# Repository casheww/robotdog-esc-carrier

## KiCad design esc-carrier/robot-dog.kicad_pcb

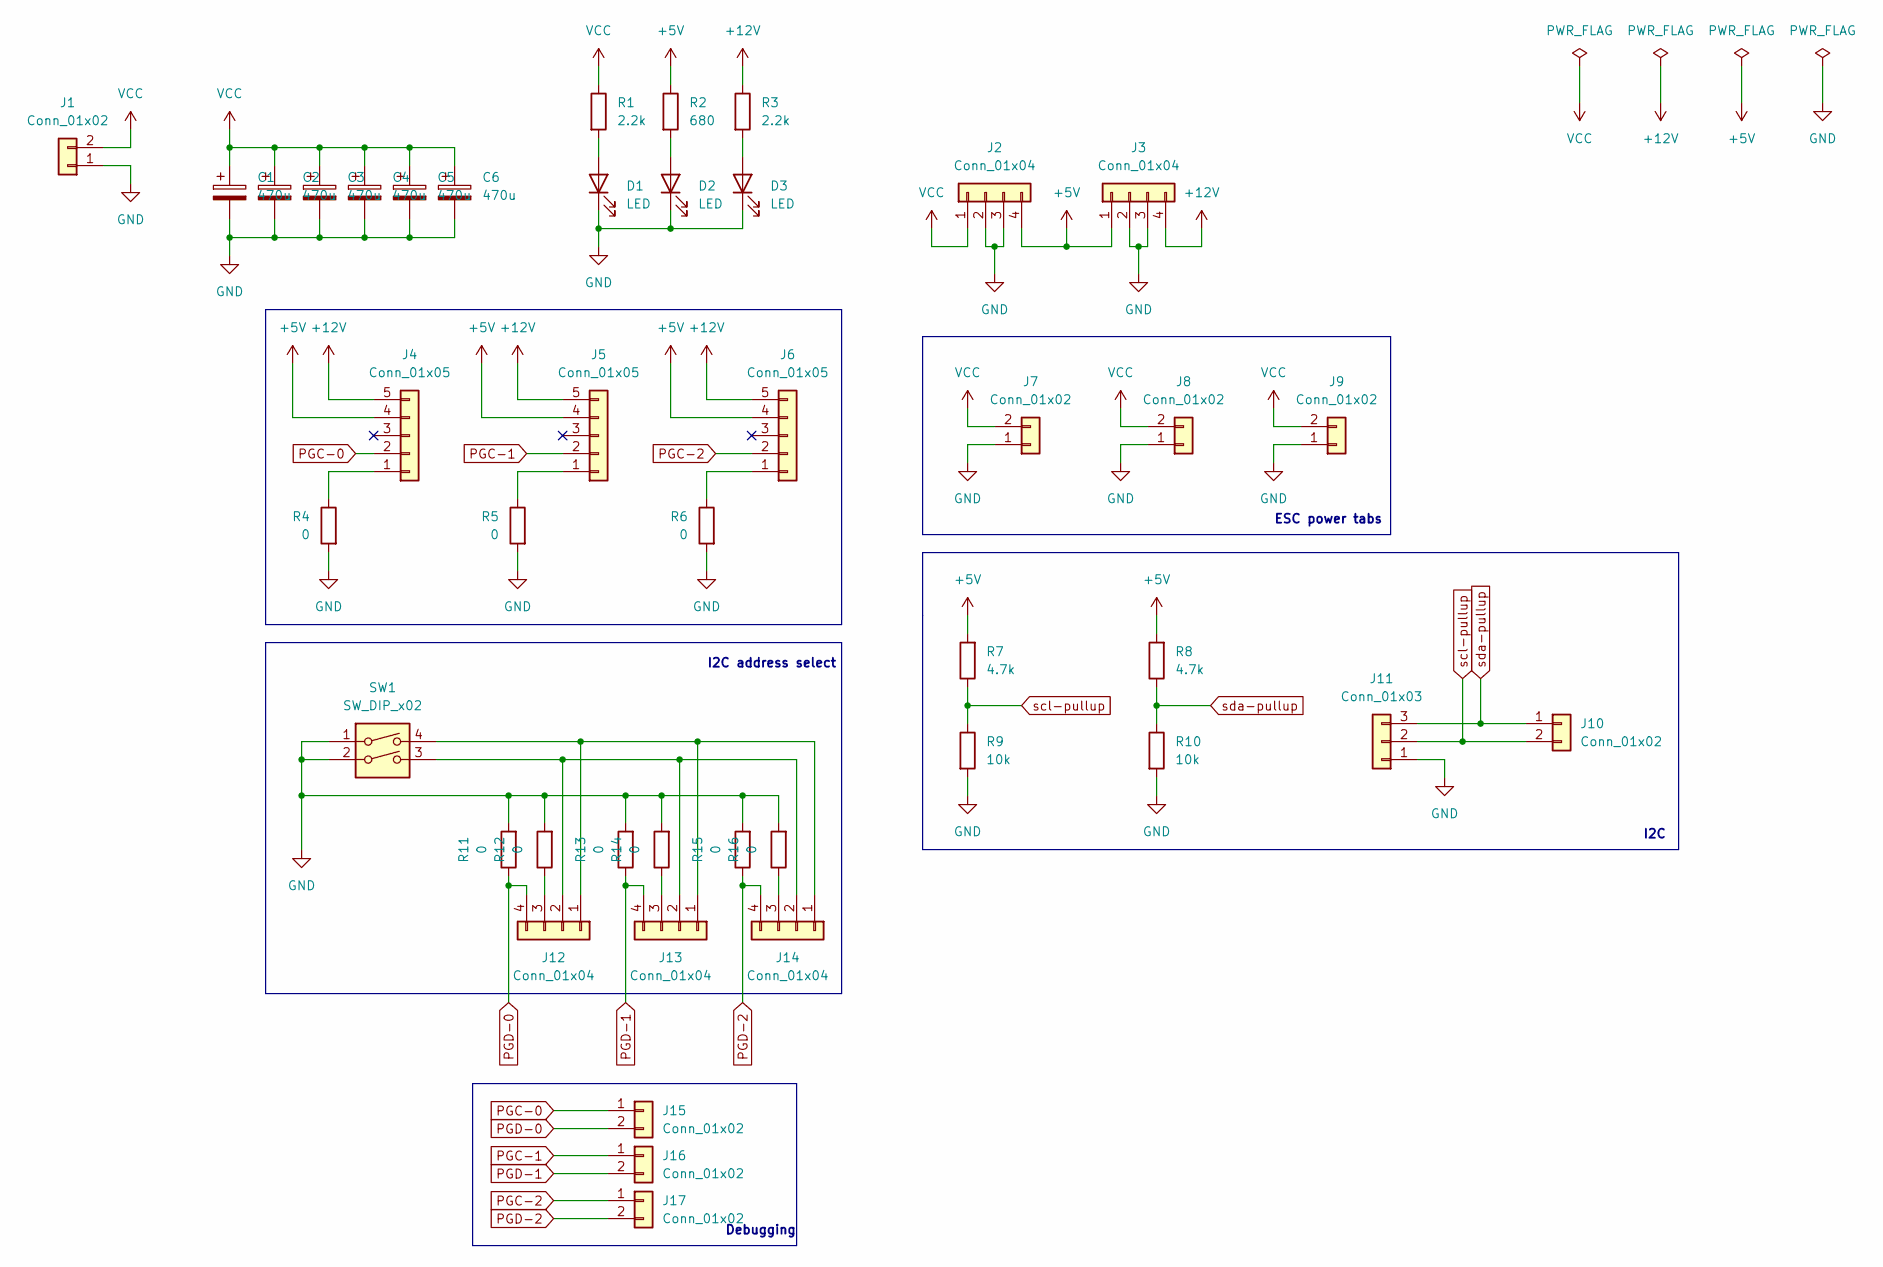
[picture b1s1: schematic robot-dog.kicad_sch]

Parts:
C1, C2, C3, C4, C5, C6: 470u; CP_Radial_D10.0mm_P3.50mm
D1, D2, D3: LED; LED_0603_1608Metric_Pad1.05x0.95mm_HandSolder
J1: Conn_01x02; AMASS_XT60-M_1x02_P7.20mm_Vertical
J2, J3: Conn_01x04; PinHeader_1x04_P2.54mm_Vertical
J4, J5, J6: Conn_01x05; ESC-I2C-Pads
J7, J8, J9: Conn_01x02; ESC-Power-Tabs
J10, J15, J16, J17: Conn_01x02; PinHeader_1x02_P2.54mm_Vertical
J11: Conn_01x03; PinHeader_1x03_P2.54mm_Vertical
J12, J13, J14: Conn_01x04; ESC-I2C-Address-Select
R1, R3: 2.2k; R_0603_1608Metric_Pad0.98x0.95mm_HandSolder
R2: 680; R_0603_1608Metric_Pad0.98x0.95mm_HandSolder
R4, R5, R6, R11, R12, R13, R14, R15, R16: 0; R_0603_1608Metric_Pad0.98x0.95mm_HandSolder
R7, R8: 4.7k; R_0603_1608Metric_Pad0.98x0.95mm_HandSolder
R9, R10: 10k; R_0603_1608Metric_Pad0.98x0.95mm_HandSolder
SW1: SW_DIP_x02; SW_DIP_SPSTx02_Slide_9.78x7.26mm_W7.62mm_P2.54mm

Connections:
+5V: J2.4, J3.1, J4.4, J5.4, J6.4, R2.1, R7.2, R8.2
+12V: J3.4, J4.5, J5.5, J6.5, R3.1
GND: C1.2, C2.2, C3.2, C4.2, C5.2, C6.2, D1.1 (K), D2.1 (K), D3.1 (K), J1.1, J2.2, J2.3, J3.2, J3.3, J7.1, J8.1, J9.1, J11.1, R4.2, R5.2, R6.2, R9.2, R10.2, R11.2, R12.2, R13.2, R14.2, R15.2, R16.2, SW1.1, SW1.2
unnamed: D1.2 (A), R1.2
unnamed: D2.2 (A), R2.2
unnamed: D3.2 (A), R3.2
unnamed: J4.1, R4.1
unnamed: J5.1, R5.1
unnamed: J6.1, R6.1
unnamed: J12.1, J13.1, J14.1, SW1.4
unnamed: J12.2, J13.2, J14.2, SW1.3
unnamed: J12.3, R12.1
unnamed: J13.3, R14.1
unnamed: J14.3, R16.1
PGC-0: J4.2, J15.1
PGC-1: J5.2, J16.1
PGC-2: J6.2, J17.1
PGD-0: J12.4, J15.2, R11.1
PGD-1: J13.4, J16.2, R13.1
PGD-2: J14.4, J17.2, R15.1
VCC: C1.1, C2.1, C3.1, C4.1, C5.1, C6.1, J1.2, J2.1, J7.2, J8.2, J9.2, R1.1
scl-pullup: J10.2, J11.2, R7.1, R9.1
sda-pullup: J10.1, J11.3, R8.1, R10.1

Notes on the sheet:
Debugging
I2C address select
I2C
ESC power tabs

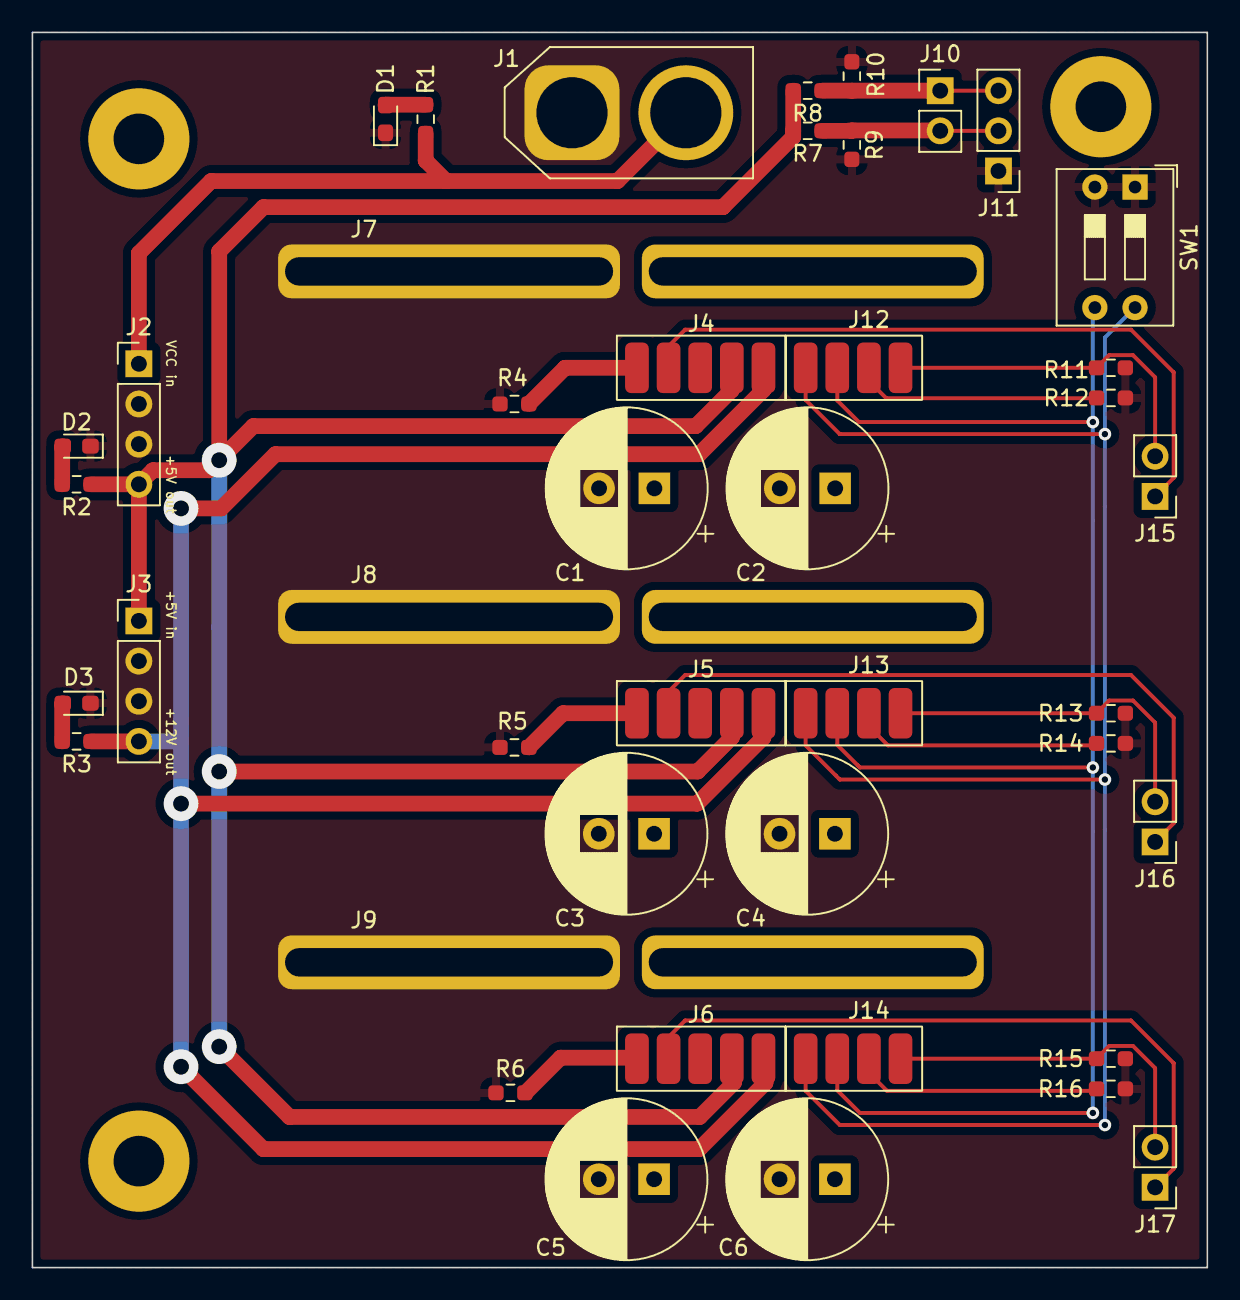
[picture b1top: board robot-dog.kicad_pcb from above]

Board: 2 copper layers, 74.3 x 78.1 mm, 43 parts (0 on the bottom side), 23 nets.

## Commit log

2022-11-18 add schematic and draft layout
2022-11-19 start trace routing
2022-11-25 fix intersecting courtyard
2022-11-28 rearrange layout
2022-11-29 add vias between gnd planes
2022-11-29 make voltage converter footprints tht
2022-12-02 adjust control board pos
2022-12-05 Final version for manufacture
2023-02-09 fix power tab orientation
2023-02-11 reroute i2c
2023-02-11 fix message 5v trace
2023-02-11 edit silkscreen
2023-02-11 give capacitors solid pour connections
2023-02-23 add optional i2c pullups
2023-02-23 move i2c lines
2023-02-23 add debugging points
2023-02-23 update PCB layout for i2c pullup/pin change and debugging pins
